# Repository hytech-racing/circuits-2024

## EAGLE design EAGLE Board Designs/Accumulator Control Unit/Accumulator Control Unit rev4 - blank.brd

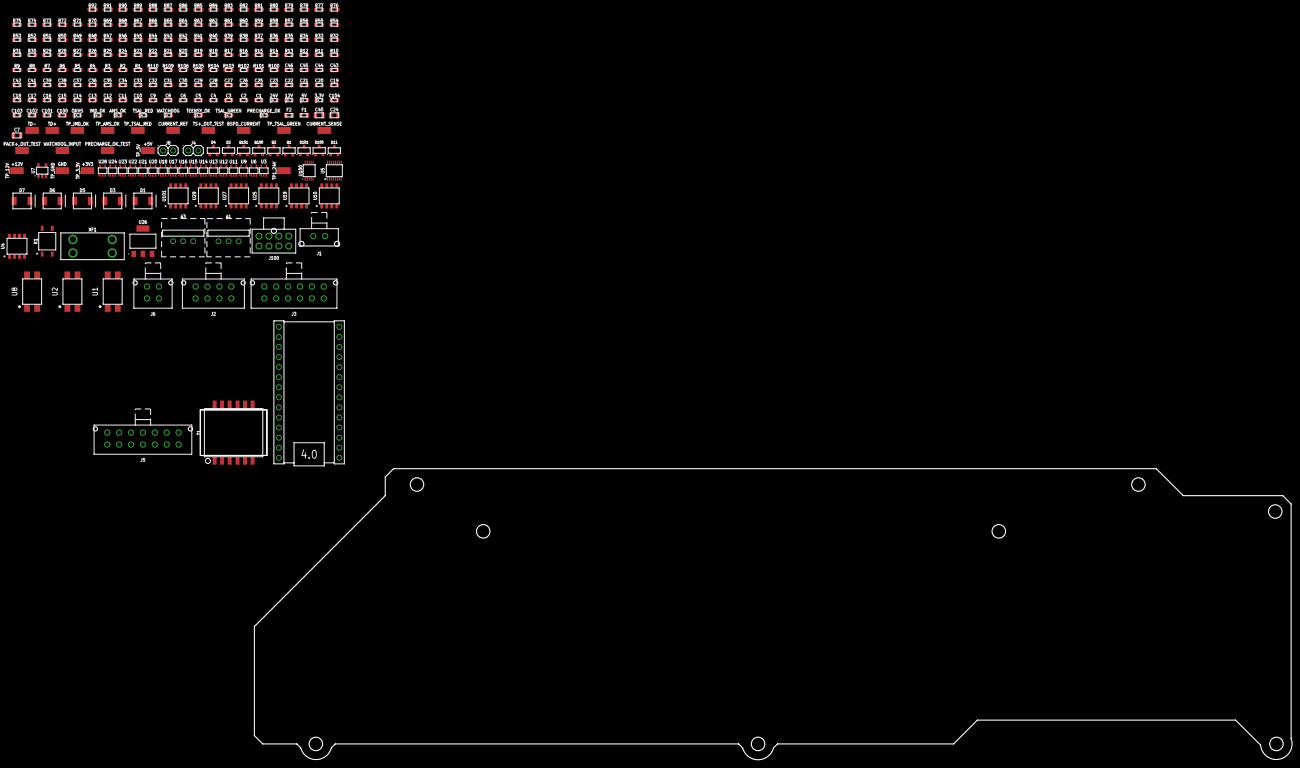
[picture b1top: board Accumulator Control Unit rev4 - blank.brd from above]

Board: 2 copper layers, 275.3 x 88.2 mm, 251 parts (0 on the bottom side), 129 nets, no tracks yet.

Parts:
3.3V: LED_0603_GREEN; 0603-LED
5V: LED_0603_BLUE; 0603-LED
12V: LED_0603_RED; 0603-LED
24V: LED_0603_ORANGE; 0603-LED
A1: VOLTAGE_REGULATOR_MODULE_OKI-78SR_5V; OKI-78SR
A2: TEENSY_4.0; TEENSY_SHORT
A3: VOLTAGE_REGULATOR_MODULE_OKI-78SR_12V; OKI-78SR
AMS_OK: LED_0603_GREEN; 0603-LED
BSPD_CURRENT: TEST_POINT; MICRO_MINIATURE
C1, C6, C100: CAPACITOR_0603_10V_10NF; 0603-CAP
C2, C20, C102: CAPACITOR_0603_25V_0.1UF; 0603-CAP
C3, C5, C8, C9, C10, C11, C13, C14, C15, C16, C17, C18, C19, C21, C22, C26, C27, C28, C29, C30, C31, C34, C38, C42, C43, C46: CAPACITOR_0603_10V_0.1UF; 0603-CAP
C4, C12, C23, C32: CAPACITOR_0603_10V_680PF; 0603-CAP
C7, C24, C40: CAPACITOR_0805_50V_10UF; 0805-CAP
C25, C45: CAPACITOR_0603_10V_4.7NF; 0603-CAP
C33: CAPACITOR_0603_25V_10UF; 0603-CAP
C35, C41: CAPACITOR_0603_50V_0.1UF; 0603-CAP
C36, C103: CAPACITOR_0603_10V_4.7UF; 0603-CAP
C37, C39, C44: CAPACITOR_0603_10V_1UF; 0603-CAP
C101, C104: CAPACITOR_0603_25V_1UF; 0603-CAP
CURRENT_REF: TEST_POINT; MICRO_MINIATURE
CURRENT_SENSE: TEST_POINT; MICRO_MINIATURE
D1, D3, D5, D6, D7: TVS_30VDO-214AA; DO-214AA
D2, D4: TVS_8V; SOT-23
D11, D100, D101: TVS_15V; SOT-23
F1, F2: FUSE_0603_.75A; 0603-FUSE
IMD_OK: LED_0603_ORANGE; 0603-LED
J1: CONNECTOR-2_MF_T_V_; MOLEX_MICROFIT_PTH_VERTICAL_02_SINGLE
J2: CONNECTOR-8_MF_T_V_; MOLEX_MICROFIT_PTH_VERTICAL_08_DUAL
J3: CONNECTOR-12_MF_T_V_; MOLEX_MICROFIT_PTH_VERTICAL_12_DUAL
J4, J8: JUMPER__1X02; 1X02
J5: CONNECTOR-14_MF_T_V_; MOLEX_MICROFIT_PTH_VERTICAL_14_DUAL
J6: CONNECTOR-4_μF_T_V_BLACK; MOLEX_MICROFIT_PTH_VERTICAL_04_DUAL
J100: CONNECTOR-8_NF_T_V_NATURAL; MOLEX_NANOFIT_PTH_08
K1: RELAY_SOLIDSTATE_NO_CPC1020NTR; SOP-04
OKHS: LED_0603_YELLOW; 0603-LED
PACK+_OUT_TEST: TEST_POINT; MICRO_MINIATURE
PRECHARGE_OK: LED_0603_RED; 0603-LED
PRECHARGE_OK_TEST: TEST_POINT; MICRO_MINIATURE
Q1, Q2, Q100, Q101: TRANSISTOR_N_MOS__PMV15ENEA; SOT-23
R1: RESISTOR_0603_120; 0603-RES
R2, R3, R9, R32, R33, R61, R62: RESISTOR_0603_2K; 0603-RES
R4, R7, R8, R21, R80, R84: RESISTOR_0603_5.1K; 0603-RES
R5, R79, R85: RESISTOR_0603_33K; 0603-RES
R6, R12: RESISTOR_0603_20K; 0603-RES
R10, R11, R16, R19, R24, R25, R49, R63: RESISTOR_0603_1K; 0603-RES
R13, R18, R103, R104: RESISTOR_0603_10; 0603-RES
R14, R17, R22, R26, R27, R29, R30, R37, R42, R43, R44, R50, R52, R55, R69, R71, R73, R77, R81, R82, R92, R100, R101, R102, R106: RESISTOR_0603_10K; 0603-RES
R15, R90: RESISTOR_0603_2.2K; 0603-RES
R20, R110: RESISTOR_0603_; 0603-RES
R23, R31, R56, R78: RESISTOR_0603_12K; 0603-RES
R28, R34, R35: RESISTOR_0603_470; 0603-RES
R36, R60, R89, R91: RESISTOR_0603_60.4; 0603-RES
R38: RESISTOR_0603_8.66K; 0603-RES
R39: RESISTOR_0603_73.2K; 0603-RES
R40: RESISTOR_0603_1M; 0603-RES
R41, R48: RESISTOR_0603_14K; 0603-RES
R45, R47, R54, R64: RESISTOR_0603_DNP; 0603-RES
R46: RESISTOR_0603_330K; 0603-RES
R51: RESISTOR_0603_5.9K; 0603-RES
R53: RESISTOR_0603_11.5K; 0603-RES
R57, R87: RESISTOR_0603_2.74K; 0603-RES
R58, R67, R68, R75, R76, R88: RESISTOR_0603_10.5K; 0603-RES
R59, R86: RESISTOR_0603_100K; 0603-RES
R65, R66, R72, R74: RESISTOR_0603_13K; 0603-RES
R70: RESISTOR_0603_36.5K; 0603-RES
R83: RESISTOR_0603_3.3K; 0603-RES
R105: RESISTOR_0603_43K; 0603-RES
R109: RESISTOR_0603_18.7K; 0603-RES
T1: TRANSFORMER_HM2112ZNLT_AIRGAP; HM2112ZNLT_AIRGAP
TD+: TEST_POINT; MICRO_MINIATURE
TD-: TEST_POINT; MICRO_MINIATURE
TEENSY_OK: LED_0603_RED; 0603-LED
TP1_24V: TEST_POINT; 5015
TP_3.3V, TP_5V, TP_12V: TEST_POINT; 5015
TP_AMS_OK: TEST_POINT; MICRO_MINIATURE
TP_GND: TEST_POINT; 5015
TP_IMD_OK: TEST_POINT; MICRO_MINIATURE
TP_TSAL_GREEN: TEST_POINT; MICRO_MINIATURE
TP_TSAL_RED: TEST_POINT; MICRO_MINIATURE
TS+_OUT_TEST: TEST_POINT; MICRO_MINIATURE
TSAL_GREEN: LED_0603_GREEN; 0603-LED
TSAL_RED: LED_0603_RED; 0603-LED
U1, U2, U8: RELAY_SOLIDSTATE_NO_DIP-4; DIP-4
U3, U9, U11, U13, U15, U17, U18, U20, U21, U22, U23, U24, U28: OPAMP_1_CHANNEL_OPA991; SC-70-5
U4, U10, U19, U25: MAX7404; SOIC-08(NARROW,0.15")
U5: LTC6820; MSOP-16
U6: LOGICGATE_BUFFER; SC-70-5
U7: ADM8316WBX30; SOT-23-5
U12, U14, U16: LOGICGATE_AND_DCK3; SC-70-5
U26: VOLTAGE_REGULATOR_SOT-223_3.3V; SOT-223
U27, U29: TCAN1051HQV-Q1; SOIC-08(NARROW,0.15")
U100: ADG1423; MSOP-10
U101: LM555; SOIC-08(NARROW,0.15")
U$1, U$2, U$3, U$4, U$5, U$6, U$7, U$8: MOUNTING_M3
WATCHDOG: LED_0603_BLUE; 0603-LED
WATCHDOG_INPUT: TEST_POINT; MICRO_MINIATURE
XF1: FUSE_HOLDER_MINIBLADEPTH; 3568

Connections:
0.90X_DIV: R45.2, R46.2, R70.1, U13.3
0.525V_DIV: R38.2, R39.1, R40.2, U21.3
3.305V_DIV: R51.2, R53.1, R54.2, U17.3
4.66V_DIV_A: R41.2, R63.1, R64.1, U11.1
4.66V_DIV_B: R47.1, R48.2, R49.1, U15.1
24VIN: D1.2, J5.1, XF1.1, XF1.2
24V_SCALED_3.3V: A2.D19, R84.1, R85.2
60V_THRESHOLD: R37.2, U21.4, U100.6, U100.7
+3V3: 3.3V.2, A2.3.3V, C2.1, C5.1, C6.2, C8.1, C9.1, C10.1, C20.1, C21.1, C29.1, C30.1, C34.2, C36.1, C42.2, C46.2, R32.2, R33.2, TP_3.3V.1, U3.5, U4.4, U4.7, U5.1, U5.6, U5.7, U5.8, U5.9, U5.12, U6.5, U7.5, U9.5, U10.4, U10.7, U18.5, U19.4, U19.7, U24.5, U25.4, U25.7, U26.2, U26.4, U27.5, U29.5
+5V: 5V.2, A1.3, A2.VIN, C13.1, C14.1, C15.1, C16.1, C17.1, C18.1, C19.1, C26.1, C27.1, C28.1, C33.1, C37.1, C38.2, C39.2, C43.2, C44.2, J3.3, R39.2, R47.2, R49.2, R53.2, R63.2, R64.2, TP_5V.1, U8.4, U11.5, U12.5, U13.5, U14.5, U15.5, U16.5, U17.5, U21.5, U22.5, U23.5, U26.3, U27.3, U29.3
+12V: 12V.2, A3.3, C40.1, C101.1, C102.1, C104.1, R61.1, R62.1, R106.2, TP_12V.1, U100.1, U100.2, U100.5, U101.8
+24V: 24V.2, A1.1, A3.1, C7.1, C24.1, C35.1, C41.1, D6.2, J2.1, J3.5, J6.1, J100.5, K1.4, R7.2, R85.1, TP1_24V.1, U1.4, U2.4, U20.5, U28.5, XF1.3, XF1.4
ACCUMULATOR_GND: J2.7, J3.12
AIR2-: J3.11, Q2.3
AMS_OK: AMS_OK.2, J5.6, R12.2, TP_AMS_OK.1, U2.3
AMS_OK_3.3V: D2.3, R13.1, R14.1, U6.4
BSPD_CURRENT: BSPD_CURRENT.1, D7.2, J5.10, R58.2, R79.1, U20.4
BSPD_CURRENT_REF: J5.11, R88.2, U28.4
BSPD_CURRENT_TEENSY: A2.D14, R79.2, R80.1
CANH: J4.1, J5.9, U27.7
CANH/1.3B: J4.2, R36.2
CANL: J5.8, R60.2, U27.6
CHASSIS_GND: J2.6, J5.13
CS_LTC_6820: A2.D10, U5.5
CURRENT: CURRENT_SENSE.1, J3.6, R30.1, R59.2, U20.1
CURRENT_BUFFER: U9.3, U9.4, U10.2
CURRENT_FILTERED: A2.D21, U10.5
CURRENT_REF: CURRENT_REF.1, J3.7, R22.1, R86.2, U28.1
CURRENT_REF_BUFFER: U3.3, U3.4, U4.2
CURRENT_REF_FILTERED: A2.D20, U4.5
EM_CANH: J6.2, J8.1, U29.7
EM_CANL: J6.3, R89.2, U29.6
EM_CRX: A2.D23, U29.4
EM_CTX: A2.D22, U29.1
GND: A1.2, A2.AGND/GND, A2.GND, A3.2, C1.2, C2.2, C3.2, C4.2, C5.2, C6.1, C7.2, C8.2, C9.2, C10.2, C11.2, C12.2, C13.2, C14.2, C15.2, C16.2, C17.2, C18.2, C19.2, C20.2, C21.2, C22.2, C23.2, C24.2, C25.1, C26.2, C27.2, C28.2, C29.2, C30.2, C31.2, C32.2, C33.2, C34.1, C35.2, C36.2, C37.2, C38.1, C39.1, C40.2, C41.2, C42.1, C43.1, C44.1, C45.1, C46.1, C100.2, C101.2, C102.2, C103.2, C104.2, D1.1, D2.1, D3.1, D4.1, D5.1, D6.1, D7.1, D11.1, D100.1, D101.1, J2.4, J3.2, J3.4, J3.9, J5.12, J6.4, J100.8, K1.2, PRECHARGE_OK.1, Q1.2, Q2.2, Q100.2, Q101.2, R2.1, R3.1, R4.2, R6.1, R9.1, R10.1, R11.1, R12.1, R14.2, R15.1, R17.2, R19.1, R21.2, R23.2, R24.2, R26.1, R27.1, R29.1, R31.2, R37.1, R38.1, R40.1, R41.1, R42.1, R43.1, R44.1, R45.1, R46.1, R48.1, R50.1, R51.1, R52.1, R54.1, R56.2, R57.1, R59.1, R65.2, R69.1, R71.1, R72.2, R73.1, R78.2, R80.2, R81.1, R82.1, R83.1, R84.2, R86.1, R87.1, R90.1, R100.1, R101.2, R102.2, R110.2, TEENSY_OK.1, TP_GND.1, U1.2, U3.2, U4.3, U5.13, U5.14, U6.3, U7.2, U8.2, U9.2, U10.3, U11.2, U12.3, U13.2, U14.3, U15.2, U16.3, U17.2, U18.2, U19.3, U20.2, U21.2, U22.2, U23.2, U24.2, U25.3, U26.1, U27.2, U27.8, U28.2, U29.2, U29.8, U100.4, U100.8, U101.1, WATCHDOG.1
HV+_OUT_OK: R43.2, U12.4, U14.1
IM: T1.10, U5.10
IMD_OK: D5.2, IMD_OK.2, J5.7, R5.1, R6.2, TP_IMD_OK.1, U1.3
IMD_OK_TEENSY: A2.D16, R4.1, R5.2
INVERTER_24V: J3.1, K1.3
INVERTER_EN: J5.2, R92.1
IP: T1.12, U5.11
ISO_PACK+: J100.1, R75.1
ISO_PACK-: J100.2, R73.2, R76.1
ISO_TS+: J100.3, R67.1
ISO_TS-: J100.4, R68.1, R81.2
MHS: D3.2, J2.3, R15.2, R20.1
MHS_TEENSY: A2.D7, R20.2, R21.1
unnamed: 3.3V.1, R19.2
unnamed: 5V.1, R10.2
unnamed: C103.1, R105.1, U101.2, U101.6
unnamed: PRECHARGE_OK.2, R16.1
unnamed: C100.1, U101.5
unnamed: R105.2, R106.1, U101.7
unnamed: Q2.1, R18.2
unnamed: R8.2, U1.1
unnamed: OKHS.1, R9.2
unnamed: R65.1, R67.2, U22.1
unnamed: R66.1, R68.2, U22.3
unnamed: R57.2, R58.1, U20.3
unnamed: A2.D11, R33.1, U5.2
unnamed: 12V.1, R11.2
unnamed: R82.2, U6.2, U7.1
unnamed: R7.1, U2.1
unnamed: AMS_OK.1, R3.2
unnamed: D100.3, R102.1, R104.1, TP_TSAL_GREEN.1, U100.9
unnamed: D101.3, R101.1, R103.1, TP_TSAL_RED.1, U101.3
unnamed: Q1.3, U2.2
unnamed: C25.2, R36.1, R60.1
unnamed: R72.1, R75.2, U23.1
unnamed: R74.1, R76.2, U23.3
unnamed: R62.2, TSAL_GREEN.2
unnamed: A2.D0, A2.D4, U27.4
unnamed: C31.1, U25.1, U25.6
unnamed: IMD_OK.1, R2.2
unnamed: F2.1, J5.3
unnamed: A2.D1, A2.D3, U27.1
unnamed: Q1.1, R13.2
unnamed: F1.1, J5.4
unnamed: 24V.1, R83.2
unnamed: R87.2, R88.1, U28.3
unnamed: C45.2, R89.1, R91.1
unnamed: J8.2, R91.2
unnamed: R25.1, U5.16
unnamed: R24.1, R25.2, U5.15
unnamed: K1.1, R92.2
unnamed: C1.1, T1.11
unnamed: R28.1, U14.4
unnamed: A2.D12, R32.1, U5.3
unnamed: A2.D13, U5.4
unnamed: C32.1, U25.8
unnamed: R61.2, TSAL_RED.2
unnamed: R34.1, WATCHDOG.2
unnamed: R77.2, R78.1, U24.1
unnamed: R28.2, U8.1
unnamed: C11.1, U10.1, U10.6
unnamed: C12.1, U10.8
unnamed: R30.2, R31.1, U9.1
unnamed: C3.1, U4.1, U4.6
unnamed: C4.1, U4.8
unnamed: R22.2, R23.1, U3.1
unnamed: C22.1, U19.1, U19.6
unnamed: C23.1, U19.8
unnamed: R55.2, R56.1, U18.1
unnamed: R35.1, TEENSY_OK.2
unnamed: Q100.1, R103.2
unnamed: Q101.1, R104.2
OKHS: J2.2, OKHS.2, R8.1, R90.2
PACK+_BUFFER: U18.3, U18.4, U19.2
PACK+_FILTERED: A2.D17, U19.5
PACK+_OUT: PACK+_OUT_TEST.1, R55.1, R70.2, R71.2, R74.2, U15.3, U17.1, U23.4
PRECHARGE+_OUT_OK: R29.2, U14.2, U16.4
PRECHARGE_OK: D4.3, D11.3, J100.7, PRECHARGE_OK_TEST.1, R16.2, R17.1, R18.1, R109.1, U8.3
PRECHARGE_OK_TEENSY: A2.D15, R109.2, R110.1
PRECHARGE_REACHED: R44.2, U12.2, U13.4
SHDN: J3.8, J5.5, J100.6
TD+: J1.1, R1.2, T1.1, TD+.1
TD-: J1.2, R1.1, T1.3, TD-.1
TEENSY_OK: A2.D6, R27.2, R35.2, U7.3
TIMER_EN: R100.2, U100.10, U101.4
TS+_OUT: R66.2, R69.2, R77.1, TS+_OUT_TEST.1, U11.3, U13.1, U21.1, U22.4
TS+_OUT_BUFFER: U24.3, U24.4, U25.2
TS+_OUT_FILTERED: A2.D18, U25.5
TS+_OUT_OV_OK: R42.2, U11.4, U12.1
TSAL_GREEN: F2.2, Q101.3, TSAL_GREEN.1
TSAL_RED: F1.2, Q100.3, TSAL_RED.1
V_PACK_REF_OV_OK: R50.2, U15.4, U16.1
V_PACK_REF_UV_OK: R52.2, U16.2, U17.4
WATCHDOG_INPUT: A2.D5, R26.2, R34.2, U7.4, WATCHDOG_INPUT.1

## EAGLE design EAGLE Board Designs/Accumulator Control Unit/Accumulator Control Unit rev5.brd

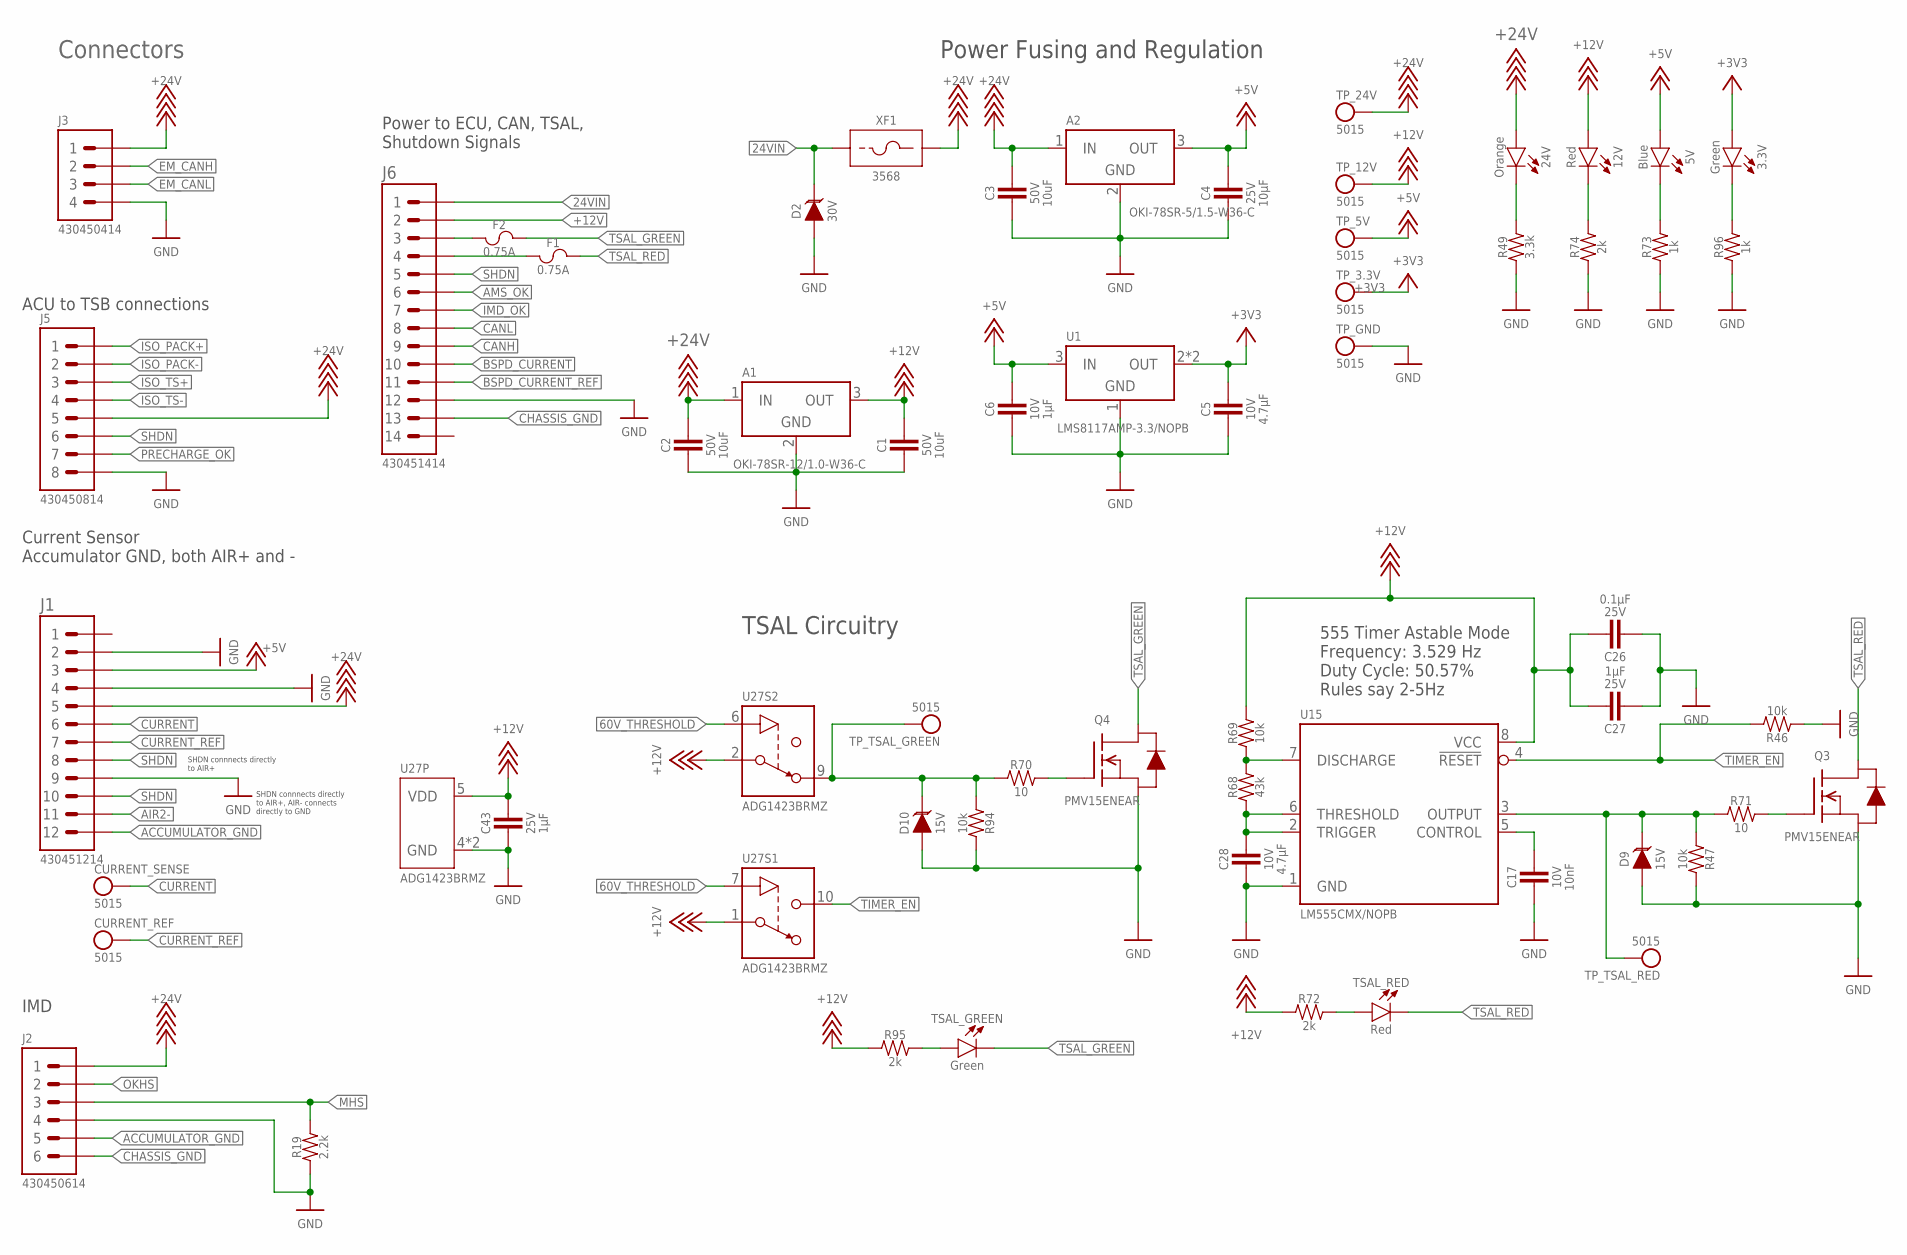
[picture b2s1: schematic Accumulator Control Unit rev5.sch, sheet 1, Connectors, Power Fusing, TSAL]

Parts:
3.3V: LED_0603_GREEN; 0603-LED
5V: LED_0603_BLUE; 0603-LED
12V: LED_0603_RED; 0603-LED
24V: LED_0603_ORANGE; 0603-LED
A1: VOLTAGE_REGULATOR_MODULE_OKI-78SR_12V; OKI-78SR
A2: VOLTAGE_REGULATOR_MODULE_OKI-78SR_5V; OKI-78SR
C1, C2, C3: CAPACITOR_0805_50V_10UF; 0805-CAP
C4: CAPACITOR_0603_25V_10UF; 0603-CAP
C5, C28: CAPACITOR_0603_10V_4.7UF; 0603-CAP
C6: CAPACITOR_0603_10V_1UF; 0603-CAP
C17: CAPACITOR_0603_10V_10NF; 0603-CAP
C26: CAPACITOR_0603_25V_0.1UF; 0603-CAP
C27, C43: CAPACITOR_0603_25V_1UF; 0603-CAP
CURRENT_REF: TEST_POINT; MICRO_MINIATURE
CURRENT_SENSE: TEST_POINT; MICRO_MINIATURE
D2: TVS_DO-214AA_30V; DO-214AA
D9, D10: TVS__15V; SOT-23
F1, F2: FUSE_0603_.75A; 0603-FUSE
J1: CONNECTOR-12_MF_T_V_; MOLEX_MICROFIT_PTH_VERTICAL_12_DUAL
J2: CONNECTOR-6_μF_T_V_BLACK; MOLEX_MICROFIT_PTH_VERTICAL_06_DUAL
J3: CONNECTOR-4_μF_T_V_BLACK; MOLEX_MICROFIT_PTH_VERTICAL_04_DUAL
J5: CONNECTOR-8_μF_T_V_BLACK; MOLEX_MICROFIT_PTH_VERTICAL_08_DUAL
J6: CONNECTOR-14_MF_T_V_; MOLEX_MICROFIT_PTH_VERTICAL_14_DUAL
Q3, Q4: TRANSISTOR_N_MOS__PMV15ENEA; SOT-23
R19: RESISTOR_0603_2.2K; 0603-RES
R46, R47, R69, R94: RESISTOR_0603_10K; 0603-RES
R49: RESISTOR_0603_3.3K; 0603-RES
R68: RESISTOR_0603_43K; 0603-RES
R70, R71: RESISTOR_0603_10; 0603-RES
R72, R74, R95: RESISTOR_0603_2K; 0603-RES
R73, R96: RESISTOR_0603_1K; 0603-RES
TP_3.3V, TP_5V, TP_12V, TP_24V: TEST_POINT; 5015
TP_GND: TEST_POINT; 5015
TP_TSAL_GREEN: TEST_POINT; MICRO_MINIATURE
TP_TSAL_RED: TEST_POINT; MICRO_MINIATURE
TSAL_GREEN: LED_0603_GREEN; 0603-LED
TSAL_RED: LED_0603_RED; 0603-LED
U1: VOLTAGE_REGULATOR_SOT-223_3.3V; SOT-223
U15: LM555; SOIC-08(NARROW,0.15")
U27: ADG1423; MSOP-10
XF1: FUSE_HOLDER_MINIBLADEPTH; 3568

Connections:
24VIN: D2.2 (C), J6.1, XF1.1, XF1.2 (1)
60V_THRESHOLD: U27.6 (IN), U27.7 (IN); also elsewhere on the board
+3V3: 3.3V.2 (A), C5.1, TP_3.3V.1, U1.2 (OUT), U1.4 (OUT); also elsewhere on the board
+5V: 5V.2 (A), A2.3 (OUT), C4.1, C6.1, J1.3, TP_5V.1, U1.3 (IN); also elsewhere on the board
+12V: 12V.2 (A), A1.3 (OUT), C1.1, C26.1, C27.1, C43.1, J6.2, R69.2, R72.1, R95.1, TP_12V.1, U15.8 (VCC), U27.1 (S), U27.2 (S), U27.5 (VDD)
+24V: 24V.2 (A), A1.1 (IN), A2.1 (IN), C2.1, C3.1, J1.5, J2.1, J3.1, J5.5, TP_24V.1, XF1.3 (2), XF1.4 (2); also elsewhere on the board
ACCUMULATOR_GND: J1.12, J2.5
AIR2-: J1.11; also elsewhere on the board
AMS_OK: J6.6; also elsewhere on the board
BSPD_CURRENT: J6.10; also elsewhere on the board
BSPD_CURRENT_REF: J6.11; also elsewhere on the board
CANH: J6.9; also elsewhere on the board
CANL: J6.8; also elsewhere on the board
CHASSIS_GND: J2.6, J6.13
CURRENT: CURRENT_SENSE.1, J1.6; also elsewhere on the board
CURRENT_REF: CURRENT_REF.1, J1.7; also elsewhere on the board
EM_CANH: J3.2; also elsewhere on the board
EM_CANL: J3.3; also elsewhere on the board
GND: A1.2 (GND), A2.2 (GND), C1.2, C2.2, C3.2, C4.2, C5.2, C6.2, C17.2, C26.2, C27.2, C28.2, C43.2, D2.1 (A), D9.1 (A), D10.1 (A), J1.2, J1.4, J1.9, J2.4, J3.4, J5.8, J6.12, Q3.2 (S), Q4.2 (S), R19.1, R46.1, R47.2, R49.1, R73.1, R74.1, R94.2, R96.1, TP_GND.1, U1.1 (GND), U15.1 (GND), U27.4 (GND), U27.8 (GND); also elsewhere on the board
IMD_OK: J6.7; also elsewhere on the board
ISO_PACK+: J5.1; also elsewhere on the board
ISO_PACK-: J5.2; also elsewhere on the board
ISO_TS+: J5.3; also elsewhere on the board
ISO_TS-: J5.4; also elsewhere on the board
MHS: J2.3, R19.2; also elsewhere on the board
unnamed: 3.3V.1 (C), R96.2
unnamed: 5V.1 (C), R73.2
unnamed: C28.1, R68.1, U15.2 (TRIGGER), U15.6 (THRESHOLD)
unnamed: C17.1, U15.5 (CONTROL)
unnamed: R68.2, R69.1, U15.7 (DISCHARGE)
unnamed: 12V.1 (C), R74.2
unnamed: D10.3 (C), R70.1, R94.1, TP_TSAL_GREEN.1, U27.9 (D)
unnamed: D9.3 (C), R47.1, R71.1, TP_TSAL_RED.1, U15.3 (OUTPUT)
unnamed: R95.2, TSAL_GREEN.2 (A)
unnamed: F2.1, J6.3
unnamed: F1.1, J6.4
unnamed: 24V.1 (C), R49.2
unnamed: R72.2, TSAL_RED.2 (A)
unnamed: Q3.1 (G), R71.2
unnamed: Q4.1 (G), R70.2
OKHS: J2.2; also elsewhere on the board
PRECHARGE_OK: J5.7; also elsewhere on the board
SHDN: J1.8, J1.10, J5.6, J6.5
TIMER_EN: R46.2, U15.4 (!RESET), U27.10 (D)
TSAL_GREEN: F2.2, Q4.3 (D), TSAL_GREEN.1 (C)
TSAL_RED: F1.2, Q3.3 (D), TSAL_RED.1 (C)

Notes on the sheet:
Connectors
ACU to TSB connections
Power to ECU, CAN, TSAL, Shutdown Signals
Power Fusing and Regulation
SHDN connnects directly to AIR+, AIR- connects directly to GND
TSAL Circuitry
555 Timer Astable Mode Frequency: 3.529 Hz Duty Cycle: 50.57% Rules say 2-5Hz
SHDN connnects directly to AIR+
Current Sensor Accumulator GND, both AIR+ and -
IMD

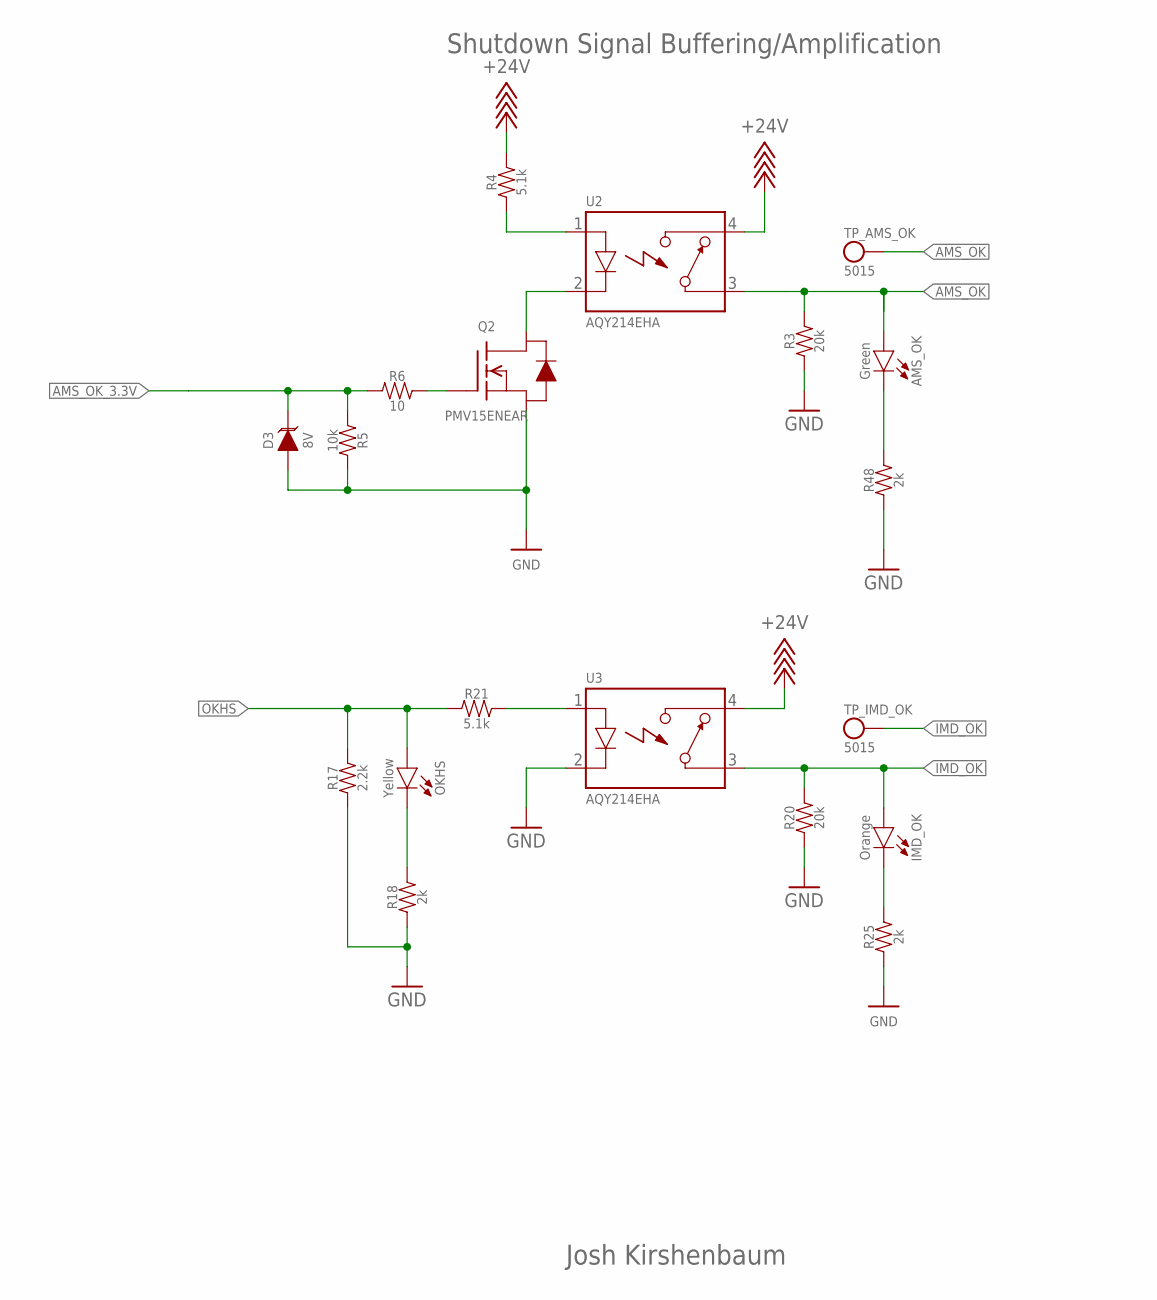
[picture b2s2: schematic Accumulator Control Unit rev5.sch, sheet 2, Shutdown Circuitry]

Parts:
AMS_OK: LED_0603_GREEN; 0603-LED
D3: TVS__8V; SOT-23
IMD_OK: LED_0603_ORANGE; 0603-LED
OKHS: LED_0603_YELLOW; 0603-LED
Q2: TRANSISTOR_N_MOS__PMV15ENEA; SOT-23
R3, R20: RESISTOR_0603_20K; 0603-RES
R4, R21: RESISTOR_0603_5.1K; 0603-RES
R5: RESISTOR_0603_10K; 0603-RES
R6: RESISTOR_0603_10; 0603-RES
R17: RESISTOR_0603_2.2K; 0603-RES
R18, R25, R48: RESISTOR_0603_2K; 0603-RES
TP_AMS_OK: TEST_POINT; MICRO_MINIATURE
TP_IMD_OK: TEST_POINT; MICRO_MINIATURE
U2, U3: RELAY_SOLIDSTATE_NO_DIP-4; DIP-4

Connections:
+24V: R4.2, U2.4 (CONTACT2), U3.4 (CONTACT2); also elsewhere on the board
AMS_OK: AMS_OK.2 (A), R3.2, TP_AMS_OK.1, U2.3 (CONTACT1); also elsewhere on the board
AMS_OK_3.3V: D3.3 (C), R5.1, R6.1; also elsewhere on the board
GND: D3.1 (A), Q2.2 (S), R3.1, R5.2, R17.1, R18.1, R20.1, R25.1, R48.1, U3.2 (CONTROL-); also elsewhere on the board
IMD_OK: IMD_OK.2 (A), R20.2, TP_IMD_OK.1, U3.3 (CONTACT1); also elsewhere on the board
unnamed: R21.2, U3.1 (CONTROL+)
unnamed: OKHS.1 (C), R18.2
unnamed: R4.1, U2.1 (CONTROL+)
unnamed: AMS_OK.1 (C), R48.2
unnamed: Q2.3 (D), U2.2 (CONTROL-)
unnamed: IMD_OK.1 (C), R25.2
unnamed: Q2.1 (G), R6.2
OKHS: OKHS.2 (A), R17.2, R21.1; also elsewhere on the board

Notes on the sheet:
Josh Kirshenbaum
Shutdown Signal Buffering/Amplification

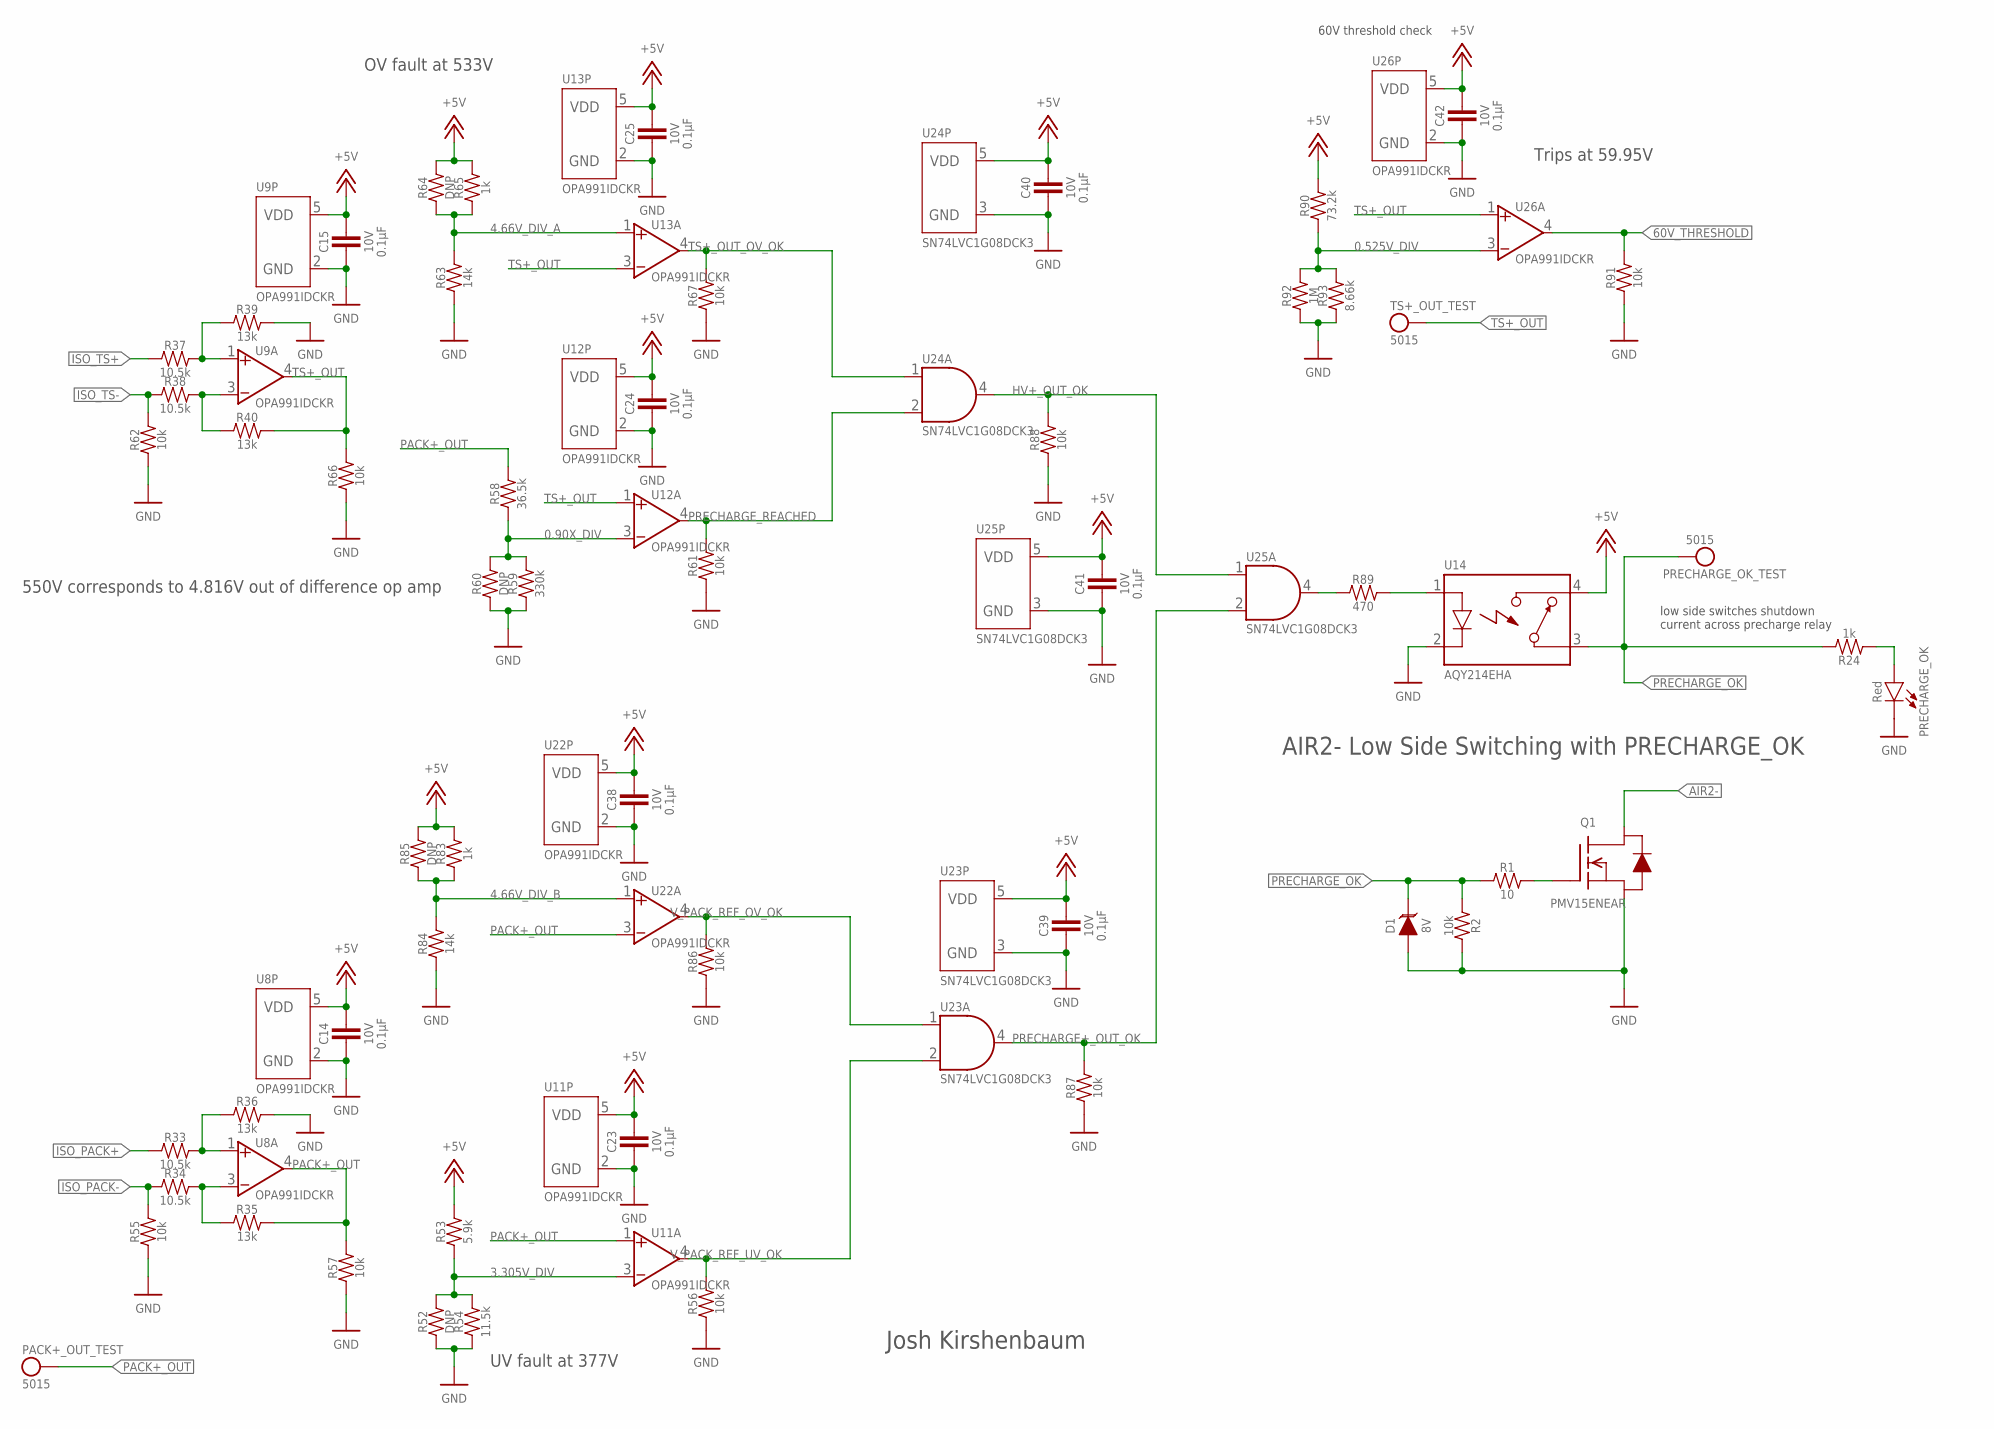
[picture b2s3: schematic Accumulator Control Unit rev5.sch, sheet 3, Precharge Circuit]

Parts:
C14, C15, C23, C24, C25, C38, C39, C40, C41, C42: CAPACITOR_0603_10V_0.1UF; 0603-CAP
D1: TVS__8V; SOT-23
PACK+_OUT_TEST: TEST_POINT; MICRO_MINIATURE
PRECHARGE_OK: LED_0603_RED; 0603-LED
PRECHARGE_OK_TEST: TEST_POINT; MICRO_MINIATURE
Q1: TRANSISTOR_N_MOS__PMV15ENEA; SOT-23
R1: RESISTOR_0603_10; 0603-RES
R2, R55, R56, R57, R61, R62, R66, R67, R86, R87, R88, R91: RESISTOR_0603_10K; 0603-RES
R24, R65, R83: RESISTOR_0603_1K; 0603-RES
R33, R34, R37, R38: RESISTOR_0603_10.5K; 0603-RES
R35, R36, R39, R40: RESISTOR_0603_13K; 0603-RES
R52, R60, R64, R85: RESISTOR_0603_DNP; 0603-RES
R53: RESISTOR_0603_5.9K; 0603-RES
R54: RESISTOR_0603_11.5K; 0603-RES
R58: RESISTOR_0603_36.5K; 0603-RES
R59: RESISTOR_0603_330K; 0603-RES
R63, R84: RESISTOR_0603_14K; 0603-RES
R89: RESISTOR_0603_470; 0603-RES
R90: RESISTOR_0603_73.2K; 0603-RES
R92: RESISTOR_0603_1M; 0603-RES
R93: RESISTOR_0603_8.66K; 0603-RES
TS+_OUT_TEST: TEST_POINT; MICRO_MINIATURE
U8, U9, U11, U12, U13, U22, U26: OPAMP_1_CHANNEL_OPA991; SC-70-5
U14: RELAY_SOLIDSTATE_NO_DIP-4; DIP-4
U23, U24, U25: LOGICGATE_AND_DCK3; SC-70-5

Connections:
0.90X_DIV: R58.1, R59.2, R60.2, U12.3 (VIN-)
0.525V_DIV: R90.1, R92.2, R93.2, U26.3 (VIN-)
3.305V_DIV: R52.2, R53.1, R54.2, U11.3 (VIN-)
4.66V_DIV_A: R63.2, R64.1, R65.1, U13.1 (VIN+)
4.66V_DIV_B: R83.1, R84.2, R85.1, U22.1 (VIN+)
60V_THRESHOLD: R91.2, U26.4 (VOUT); also elsewhere on the board
+5V: C14.1, C15.1, C23.1, C24.1, C25.1, C38.1, C39.1, C40.1, C41.1, C42.1, R53.2, R64.2, R65.2, R83.2, R85.2, R90.2, U8.5 (VDD), U9.5 (VDD), U11.5 (VDD), U12.5 (VDD), U13.5 (VDD), U14.4 (CONTACT2), U22.5 (VDD), U23.5 (VDD), U24.5 (VDD), U25.5 (VDD), U26.5 (VDD); also elsewhere on the board
AIR2-: Q1.3 (D); also elsewhere on the board
GND: C14.2, C15.2, C23.2, C24.2, C25.2, C38.2, C39.2, C40.2, C41.2, C42.2, D1.1 (A), PRECHARGE_OK.1 (C), Q1.2 (S), R2.2, R36.2, R39.2, R52.1, R54.1, R55.1, R56.1, R57.1, R59.1, R60.1, R61.1, R62.1, R63.1, R66.1, R67.1, R84.1, R86.1, R87.1, R88.1, R91.1, R92.1, R93.1, U8.2 (GND), U9.2 (GND), U11.2 (GND), U12.2 (GND), U13.2 (GND), U14.2 (CONTROL-), U22.2 (GND), U23.3 (GND), U24.3 (GND), U25.3 (GND), U26.2 (GND); also elsewhere on the board
HV+_OUT_OK: R88.2, U24.4 (OUT), U25.1 (IN1)
ISO_PACK+: R33.1; also elsewhere on the board
ISO_PACK-: R34.1, R55.2; also elsewhere on the board
ISO_TS+: R37.1; also elsewhere on the board
ISO_TS-: R38.1, R62.2; also elsewhere on the board
unnamed: PRECHARGE_OK.2 (A), R24.1
unnamed: Q1.1 (G), R1.2
unnamed: R37.2, R39.1, U9.1 (VIN+)
unnamed: R38.2, R40.1, U9.3 (VIN-)
unnamed: R33.2, R36.1, U8.1 (VIN+)
unnamed: R34.2, R35.1, U8.3 (VIN-)
unnamed: R89.1, U25.4 (OUT)
unnamed: R89.2, U14.1 (CONTROL+)
PACK+_OUT: PACK+_OUT_TEST.1, R35.2, R57.2, R58.2, U8.4 (VOUT), U11.1 (VIN+), U22.3 (VIN-); also elsewhere on the board
PRECHARGE+_OUT_OK: R87.2, U23.4 (OUT), U25.2 (IN2)
PRECHARGE_OK: D1.3 (C), PRECHARGE_OK_TEST.1, R1.1, R2.1, R24.2, U14.3 (CONTACT1); also elsewhere on the board
PRECHARGE_REACHED: R61.2, U12.4 (VOUT), U24.2 (IN2)
TS+_OUT: R40.2, R66.2, TS+_OUT_TEST.1, U9.4 (VOUT), U12.1 (VIN+), U13.3 (VIN-), U26.1 (VIN+); also elsewhere on the board
TS+_OUT_OV_OK: R67.2, U13.4 (VOUT), U24.1 (IN1)
V_PACK_REF_OV_OK: R86.2, U22.4 (VOUT), U23.1 (IN1)
V_PACK_REF_UV_OK: R56.2, U11.4 (VOUT), U23.2 (IN2)

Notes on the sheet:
60V threshold check
low side switches shutdown current across precharge relay
Josh Kirshenbaum
AIR2- Low Side Switching with PRECHARGE_OK
550V corresponds to 4.816V out of difference op amp
OV fault at 533V
UV fault at 377V
Trips at 59.95V
